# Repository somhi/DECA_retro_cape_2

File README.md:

# DECA Retro Cape 2

### (2 layer - MiSTer module SDRAM version)

DECA Retro Cape 2 is an addon for the [DECA FPGA](https://github.com/DECAfpga/DECA_board) development kit from Arrow/Terasic. The addon is connected to the Beaglebone Black connectors and hence the name of Cape as addons in the Beaglebone world are known.

This cape adds IO interface to the DECA board with all is needed to implement retro computers in this beautiful FPGA. Main IO interfaces are DB15 for VGA, PS2 for keyboard and mouse, DB9 for joystick, MiSTer memory connector, MiSTer user port.

Project has been developed with KiCAD 6.0. 

### Status

STATUS (29/01/23): Tests of v0.90 PCB work as expected, except for JP8 jumper (see [testing notes](testing_v0.90.md)). 

STATUS (26/12/22):  Finalized design v0.90 and production files including BOM and CPL.  See end of readme for changelog improvements from v0.71.

STATUS (07/04/22):  PCBs v0.71 received. Started [testing](testing.md).  Do not use without modifying voltage protections. Keyboard and Joystick (DB9 and USB3) protections must be redesigned in the next release.

STATUS (15/03/22):  prototype desing work finished. v0.71 gerbers sent to JLCPCB for manufacturing.

### Credits

I want to give credits to Tom Verbeure from whom I've taken his [original design  files](https://github.com/tomverbeure/arrow_deca_retro_cape) and adapted to my own design. Not much have been left from his design, but the name "DECA Retro Cape" remains.  

Thanks to rest of Hard Team DECA (C.Palmero & Rhoderik) and Telegram groups for the support received  during the development phase.

### **Schematic**

 [arrow_deca_retro_cape.pdf](arrow_deca_retro_cape.pdf) 

### **Features**

* VGA DAC 444
  *  Jumper to make use of VGA to SCART cables for 15 kHz RGB video

* Terasic 2x20 pin connector (for Mister SDRAM modules) + 3 pin for Dual SDRAM/SRAM 
* PS2 keyboard & mouse connectors
* Double Pmod (1/2) for peripherals (VGA Pmod, Hyperram, ...). 
  * Added four central pins for compatibility with RGB module of MuseLabs

* Pmod 3 (SPI + UART). Can act as Pmod host or peripheral 
* DETO Pmod (6 pin) for general usage (3 multiplexed pins)
* Game controller port (selection jumper to enable one or the other)
  * DB9 connector for joystick (Sega megadrive) (solder JP3 for A.Villena MiSTer DB9 addons)
  * USB3 User Port (for SNAC adapters SNES, Atari, ...)

* UART (Rx/Tx) header
* Power supply headers (5V, 3V3, 3V3 LDO, 2V5 LDO, 1V8 analog)

### **Important Usage notes**

* **Better do not connect/disconnect interfaces while the board is powered**
* **Do not connect two devices simultaneously into DB9 and USB3. Doing so may lead to unpredictabily results and damage the FPGA board**
* Prior to first power on it is required to solder jumpers JP2 (pins 3V3 and V) and JP7 (pin 5V and central pin). Read jumper selection notes below
* To use MiSTer memory modules place jumper JP6 to power supply 3V3 (and better left JP5 without jumper)
* Place jumper JP8 on desired interface (DB9 or USB3) for joystick usage. For USB3 jumper JP9 default is I/O.
* For USB3 SNAC adapters **do not** use the [SNAC level shifter adapter](https://manuferhi.com/p/snac-adapter-for-mister) as voltage protection is already included in the cape.
* For the rest of jumpers read jumper selection notes below. In case of doubt leave the default recommended position.
* There are a few signals with shared functions that cannot be used at the same time. Those signals are indicated in the PCB silkscreen with ( ) or *, **:
  * (1), (2) are shared between DETO PMOD and PMOD2
  * (3) is shared between DETO PMOD and the MUX signal of DB9 when JP3 is soldered
  * "**" only either DB9 or USB3 connector can be used at the same time (select it by jumper JP8)
  * "*" signals MISO, MOSI, CS2, SCK are shared between PMOD3 and the four pins of J2 and J3 located between pmods 2 & 3

### **Jumper Selection**

Defaults are OPEN (jumper not placed or not soldered) and CLOSED (jumper placed or soldered)

* JP1 jumper select Pmod 3 mode as peripheral (no jumper) or host (with jumper) [default is open]

* JP2 solder jumper selects 3V3 power supply from Deca board or from an optional LDO [default 3V3]. An optional 5V to 3V3 LDO can be soldered if the board cannot cope with the connected loads.

* JP3 solder jumper enables compatibility with Antonio Villena's MiSTer DB9 addons if soldered (MUX signal to allow two joysticks). Be careful, THIS OPTION IS UNTESTED [default open]

* JP4 jumper closed enables 5V at VGA pin 9 to make use of VGA to SCART cables for 15 kHz RGB video [default open]

* JP5 jumper closed power supply 2x20 Terasic connector with +5V [default open]

* JP6 jumper closed power supply 2x20 Terasic connector with +3V3 [default closed]

* JP7 solder jumper to select joystick power supply (5V or 2V5) [default 5V]

* JP8 jumper select either DB9 interface or USER IO (USB3). **Only one device can be connected at a time, otherwise might be damaged the FPGA board**

* JP9 jumper select USER IO pin 9 function (signal I/O or 3V3 power) [default I/O]

### 3D model

### Changelog

v0.5  routed finalized

v0.6  MiSTer SDRAM only version. Changed to 2 layer board.

v0.62 all finished except VGA R2R schematic and routing

v0.65 power header changed, minor aesthetic changes

v0.68 added vga schematic and indiv. R 0805 into layout

v0.70 routing finished including vga

v0.71 finished prototype desing. Gerber sent to JLCPCB for manufacturing

v0.72 updated pinout spreadsheet and Readme with testing notes and improvements to be done

v0.75 Improvements from testing phase. 

* Changed footprint DB15 VGA to fit connectors from Aliexpress (was needed to bend pins)

* DETO Pmod connector change to socket type instead of pin type

* Silkscreen improvements: OSHW logo top

* Removed JTAG footprint

* Change limiting resistor of 180 Ohm to 510 Ohm (ps2 and db9)

* Power header reduced to 1 row instead of 2

* Optimized some traces

* Added solder pad JP3 to enable/disable compatibility with Antonio Villena's MiSTer DB9 addons

* JP4 jumper to enable 5V at VGA pin 9 to make use of VGA to SCART cables for 15 kHz RGB video

* Added PCB Hole for seeing Conf_done, Rx, Tx leds

v0.76 Double pmod 1&2 now compatible with pmod RGB module of MuseLabs (added 4 shared pins)

v0.77 Changes:

* Terasic connector: add jumpers on 5V and 3V3 to disconnect power, so I can connect it to other Terasic powered connectors.
* Replaced 3 pin jumper JP2 with solder jumper on 3V3 power selection
* Added solder jumper to select joystick power supply (5V or 2V5 from LDO)

v0.78 Changes:

* PS2 protection usign 3V9 Zener diodes (3V7 to 4V1).

* Added pulldown optional resistors for ps2 mouse

v0.80 Added Joystick shifter level protection with IC [TXS0108E](https://jlcpcb.com/partdetail/TexasInstruments-TXS0108EPWR/C17206) and jumper JP8 to select either DB9 or USB3 IO interface

v0.81 Improved Readme. Added readme notice in silkscreen. Removed v0.78 pulldown optional resistors for ps2 mouse (one of the pins has a physical pull-up resistor in fpga, so wouldn't work).

v0.82 generated BOM before installing jlcpcb-tools plugin

v0.83 Added jlcpcb parts with jlcpcb tools plugin 

v0.84 updated USB3 footprint

v0.85 updated references folder. choose zener 3V9 reference 

v0.86 updated datasheets, added R7 1Ω for increasing ESR on 2V5 LDO output with a ceramic capacitor instead of tantalum, updated BOM and nearly finished jlcpcb parts selection

v0.87 updated readme. Minor changes on schematic and PCB 

v0.90 Finalized design v0.90 and production files including BOM and CPL

### TODO improvements

* Reduce lenght of board in VGA wing side
* PS2:  Jumpers to activate pull-down resistors to enable USB mode
* If space is needed, make a common ps2 connector for keyb and mouse (ps2 splitter should be used). 
* Jumper on joystick DB9 pin 5 to change power supply to pin 7 in order to allow other joysticks like the Amiga one to work. Comment from telegram: "El Jumper lo puedes poner para cambiar la alimentación entre pin 5 y 7. De esa forma te funcionara ok los dos y podrás conectar cosas como el ratón de amiga. De los joysticks clásicos, la mayoría son totalmente pasivos y los quickshot II utilizan la alimentación de 5v para el autofire."
* SDRAM DQ14 and DQ15 position in newer MiSTer modules (xsds) are exchanged respect the older module (xs) I based my design from. This does not affect functionality at all as data in and data out are always in the same order.

### Testing

[Testings on v0.71 PCB](testing_v0.71.md)

[Testings on v0.90 PCB](testing_v0.90.md)

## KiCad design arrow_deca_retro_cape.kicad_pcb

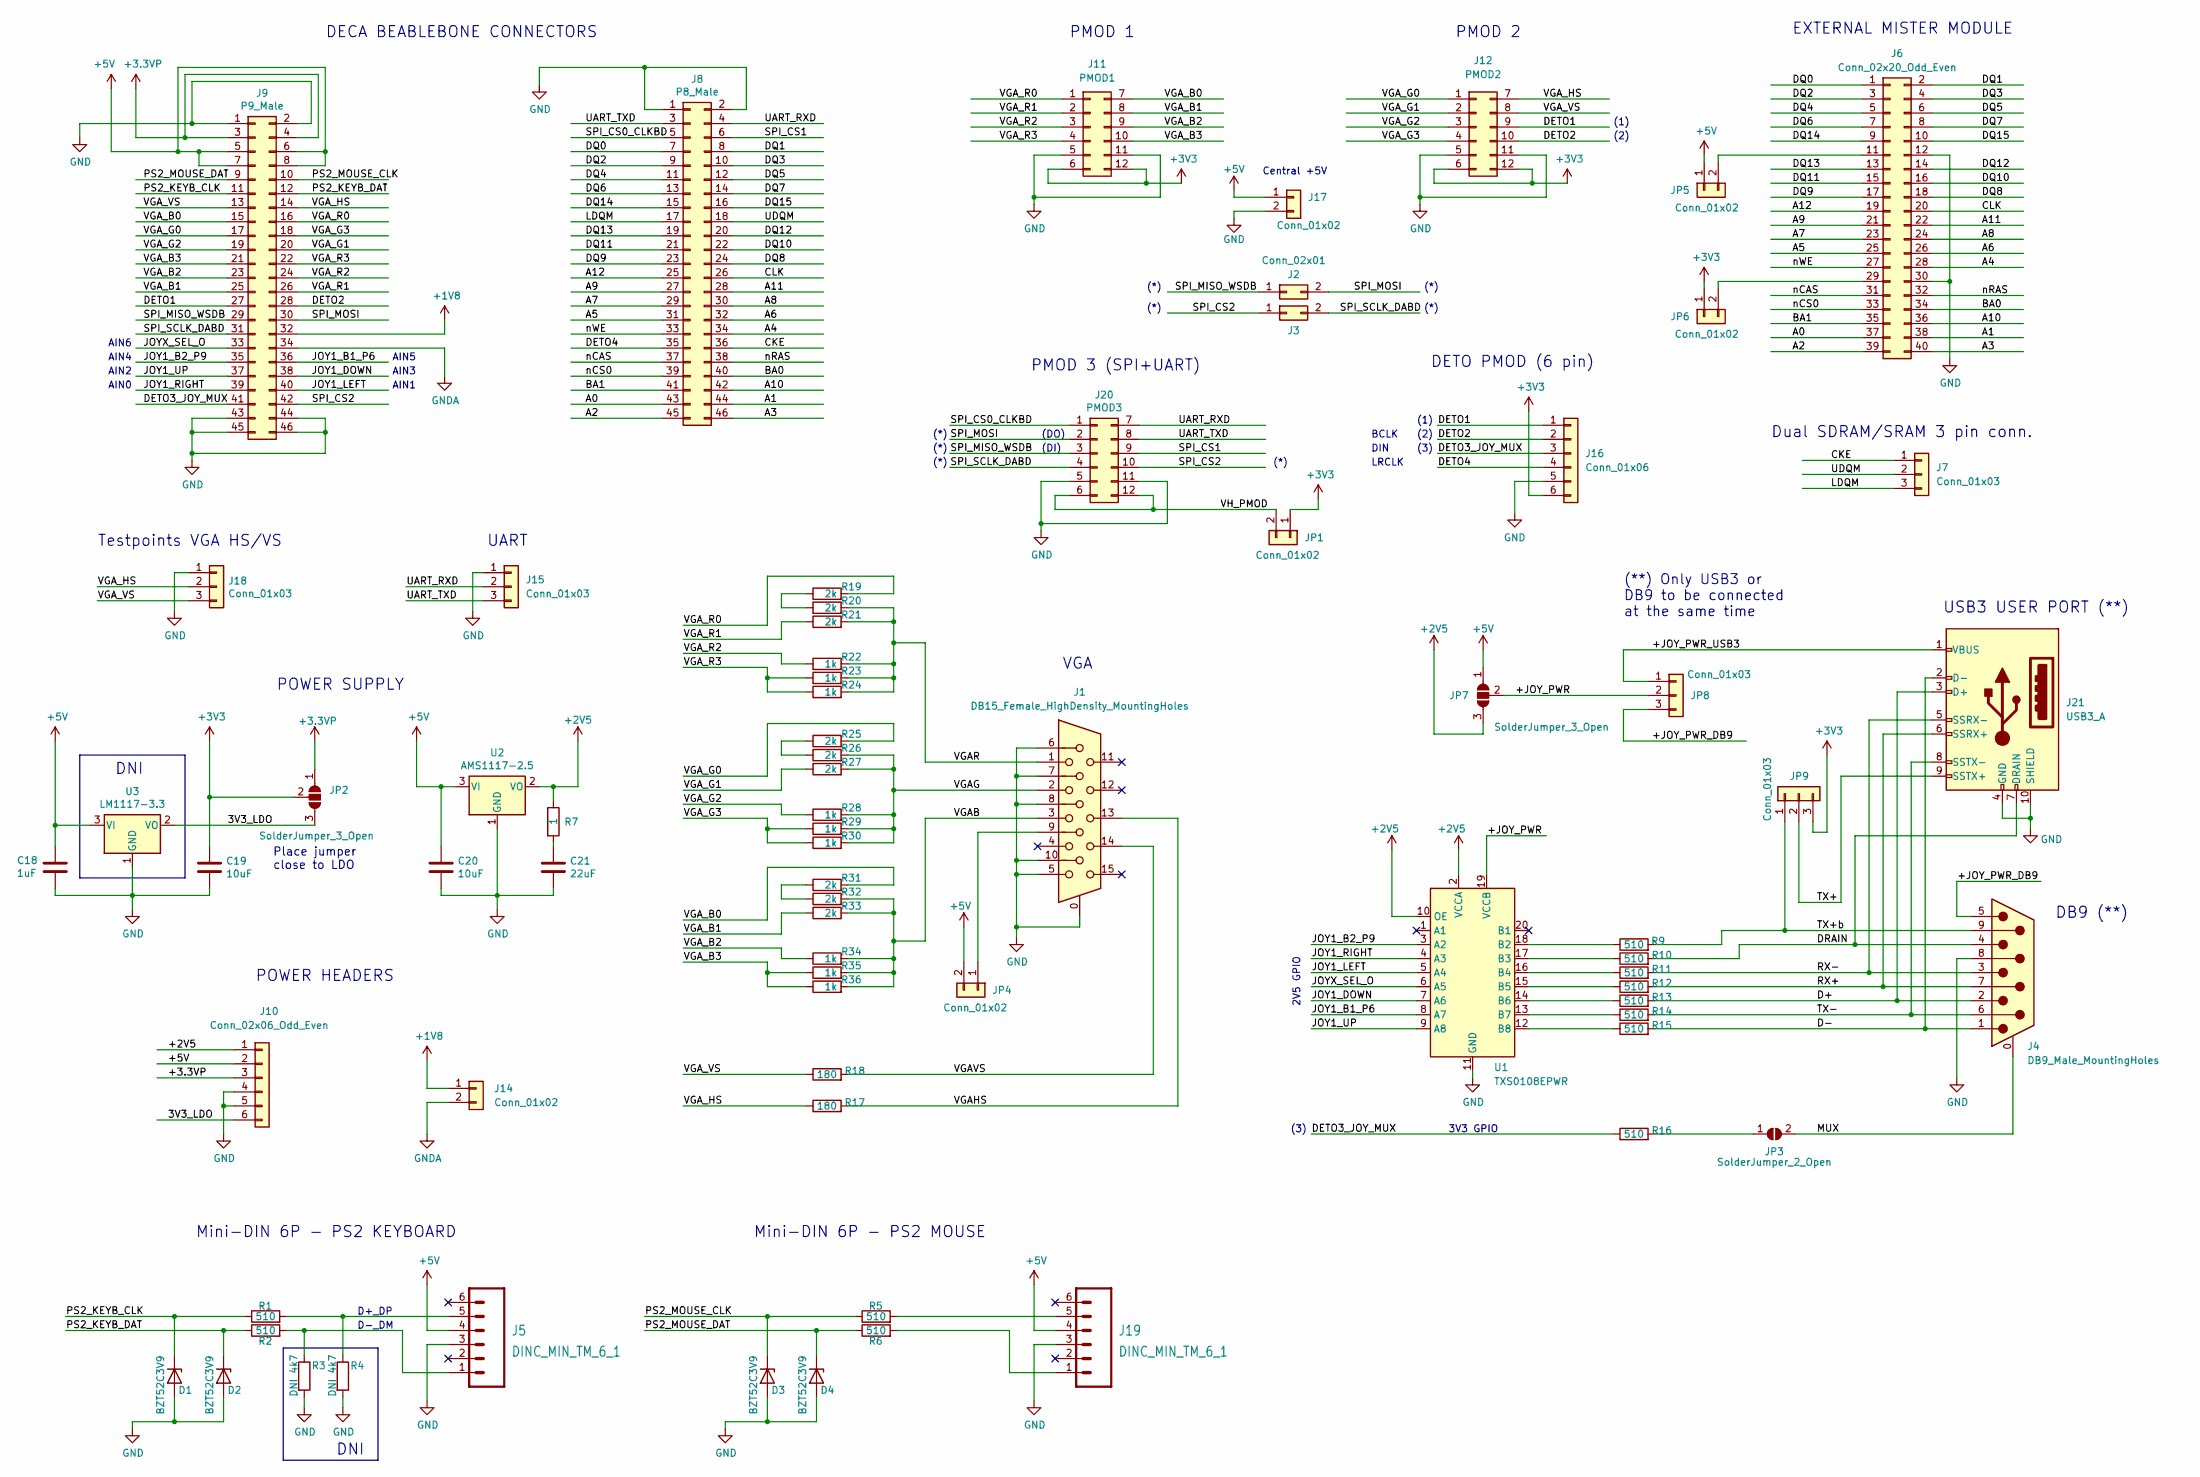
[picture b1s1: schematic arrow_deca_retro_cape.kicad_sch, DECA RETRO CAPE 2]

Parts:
C18: 1uF; C_0805_2012Metric_Pad1.18x1.45mm_HandSolder
C19, C20: 10uF; C_0805_2012Metric_Pad1.18x1.45mm_HandSolder
C21: 22uF; C_0805_2012Metric_Pad1.18x1.45mm_HandSolder
D1, D2, D3, D4: BZT52C3V9; D_SOD-123
J1: DB15_Female_HighDensity_MountingHoles; DSUB-15-HD_Female_Horizontal_P2.29x1.98mm_EdgePinOffset3.03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
J2, J3: Conn_02x01; PinSocket_1x02_P2.54mm_Vertical
J4: DB9_Male_MountingHoles; DSUB-9_Male_Horizontal_P2.77x2.84mm_EdgePinOffset9.90mm_Hou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
J5, J19: DINC_MIN_TM_6_1; DINC_MIN_TM_6_1PRIMARY
J6: Conn_02x20_Odd_Even; PinHeader_2x20_P2.54mm_Vertical
J7: Conn_01x03; PinSocket_1x03_P2.54mm_Vertical
J8: P8_Male; PinHeader_2x23_P2.54mm_Vertical
J9: P9_Male; PinHeader_2x23_P2.54mm_Vertical
J10: Conn_02x06_Odd_Even; PinSocket_1x06_P2.54mm_Vertical
J11: PMOD1; Pmod_2x06_P2.54mm_Vertical_2
J12: PMOD2; Pmod_2x06_P2.54mm_Vertical_2
J14, J17: Conn_01x02; PinSocket_1x02_P2.54mm_Vertical
J15, J18: Conn_01x03; PinHeader_1x03_P2.54mm_Vertical
J16: Conn_01x06; PinSocket_1x06_P2.54mm_Vertical
J20: PMOD3; PMOD_Female_Horizontal_2
J21: USB3_A; USB-3.0-TH_C69073
JP1, JP4, JP5, JP6: Conn_01x02; PinHeader_1x02_P2.54mm_Vertical
JP2, JP7: SolderJumper_3_Open; SolderJumper-3_P2.0mm_Open_TrianglePad1.0x1.5mm
JP3: SolderJumper_2_Open; SolderJumper-2_P1.3mm_Open_RoundedPad1.0x1.5mm
JP8, JP9: Conn_01x03; PinHeader_1x03_P2.54mm_Vertical
R1, R2, R5, R6, R9, R10, R11, R12, R13, R14, R15, R16: 510; R_0805_2012Metric_Pad1.20x1.40mm_HandSolder
R3, R4: DNI 4k7; R_0805_2012Metric_Pad1.20x1.40mm_HandSolder
R7: 1; R_0805_2012Metric_Pad1.20x1.40mm_HandSolder
R17, R18: 180; R_0805_2012Metric_Pad1.20x1.40mm_HandSolder
R19, R20, R21, R25, R26, R27, R31, R32, R33: 2k; R_0805_2012Metric_Pad1.20x1.40mm_HandSolder
R22, R23, R24, R28, R29, R30, R34, R35, R36: 1k; R_0805_2012Metric_Pad1.20x1.40mm_HandSolder
U1: TXS0108EPWR; TSSOP-20_4.4x6.5mm_P0.65mm
U2: AMS1117-2.5; SOT-223-3_TabPin2
U3: LM1117-3.3; SOT-223-3_TabPin2

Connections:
+1V8: J9.32, J14.1
+2V5: J10.1, JP7.3 (B), R7.1, U1.2 (VCCA), U1.10 (OE), U2.2 (VO)
+3.3VP: J9.3, J9.4, J10.3, JP2.1 (A)
+3V3: C19.1, J11.6, J11.12, J12.6, J12.12, J16.6, JP1.1, JP2.2 (C), JP6.1, JP9.3
+5V: C18.1, C20.1, J5.4, J9.5, J9.6, J9.7, J9.8, J10.2, J17.1, J19.4, JP4.2, JP5.1, JP7.1 (A), U2.3 (VI), U3.3 (VI)
/3V3_LDO: J10.6, JP2.3 (B), U3.2 (VO)
/+JOY_PWR: JP7.2 (C), JP8.2, U1.19 (VCCB)
/+JOY_PWR_DB9: J4.5, JP8.3
/+JOY_PWR_USB3: J21.1 (VBUS), JP8.1
/A0: J6.37, J8.43
/A1: J6.38, J8.44
/A2: J6.39, J8.45
/A3: J6.40, J8.46
/A4: J6.28, J8.34
/A5: J6.25, J8.31
/A6: J6.26, J8.32
/A7: J6.23, J8.29
/A8: J6.24, J8.30
/A9: J6.21, J8.27
/A10: J6.36, J8.42
/A11: J6.22, J8.28
/A12: J6.19, J8.25
/BA0: J6.34, J8.40
/BA1: J6.35, J8.41
/CKE: J7.1, J8.36
/CLK: J6.20, J8.26
/D+: J4.2, J21.3 (D+), R13.2
/D-: J4.1, J21.2 (D-), R15.2
/DETO1: J9.27, J12.9, J16.1
/DETO2: J9.28, J12.10, J16.2
/DETO3_JOY_MUX: J9.41, J16.3, R16.1
/DETO4: J8.35, J16.4
/DQ0: J6.1, J8.7
/DQ1: J6.2, J8.8
/DQ2: J6.3, J8.9
/DQ3: J6.4, J8.10
/DQ4: J6.5, J8.11
/DQ5: J6.6, J8.12
/DQ6: J6.7, J8.13
/DQ7: J6.8, J8.14
/DQ8: J6.18, J8.24
/DQ9: J6.17, J8.23
/DQ10: J6.16, J8.22
/DQ11: J6.15, J8.21
/DQ12: J6.14, J8.20
/DQ13: J6.13, J8.19
/DQ14: J6.9, J8.15
/DQ15: J6.10, J8.16
/DRAIN: J4.4, J21.7 (DRAIN), R10.2
/JOY1_B1_P6: J9.36, U1.8 (A7)
/JOY1_B2_P9: J9.35, U1.3 (A2)
/JOY1_DOWN: J9.38, U1.7 (A6)
/JOY1_LEFT: J9.40, U1.5 (A4)
/JOY1_RIGHT: J9.39, U1.4 (A3)
/JOY1_UP: J9.37, U1.9 (A8)
/JOYX_SEL_O: J9.33, U1.6 (A5)
/LDQM: J7.3, J8.17
/MUX: J4.0 (PAD), JP3.2 (B)
/PS2_KEYB_CLK: D1.1 (K), J9.11, R1.1
/PS2_KEYB_DAT: D2.1 (K), J9.12, R2.1
/PS2_MOUSE_CLK: D3.1 (K), J9.10, R5.1
/PS2_MOUSE_DAT: D4.1 (K), J9.9, R6.1
/RX+: J4.7, J21.6 (SSRX+), R12.2
/RX-: J4.3, J21.5 (SSRX-), R11.2
/SPI_CS0_CLKBD: J8.5, J20.1
/SPI_CS1: J8.6, J20.9
/SPI_CS2: J3.1, J9.42, J20.10
/SPI_MISO_WSDB: J2.1, J9.29, J20.3
/SPI_MOSI: J2.2, J9.30, J20.2
/SPI_SCLK_DABD: J3.2, J9.31, J20.4
/TX+: J21.9 (SSTX+), JP9.2
/TX+b: J4.9, JP9.1, R9.2
/TX-: J4.6, J21.8 (SSTX-), R14.2
/UART_RXD: J8.4, J15.2, J20.7
/UART_TXD: J8.3, J15.3, J20.8
/UDQM: J7.2, J8.18
/VGAB: J1.3, R32.2, R33.2, R34.2, R35.2, R36.2
/VGAG: J1.2, R26.2, R27.2, R28.2, R29.2, R30.2
/VGAHS: J1.13, R17.2
/VGAR: J1.1, R20.2, R21.2, R22.2, R23.2, R24.2
/VGAVS: J1.14, R18.2
/VGA_B0: J9.15, J11.7, R31.2
/VGA_B1: J9.25, J11.8, R33.1
/VGA_B2: J9.23, J11.9, R34.1
/VGA_B3: J9.21, J11.10, R35.1, R36.1
/VGA_G0: J9.17, J12.1, R25.2
/VGA_G1: J9.20, J12.2, R27.1
/VGA_G2: J9.19, J12.3, R28.1
/VGA_G3: J9.18, J12.4, R29.1, R30.1
/VGA_HS: J9.14, J12.7, J18.2, R17.1
/VGA_R0: J9.16, J11.1, R19.2
/VGA_R1: J9.26, J11.2, R21.1
/VGA_R2: J9.24, J11.3, R22.1
/VGA_R3: J9.22, J11.4, R23.1, R24.1
/VGA_VS: J9.13, J12.8, J18.3, R18.1
/VH_PMOD: J20.6, J20.12, JP1.2
/nCAS: J6.31, J8.37
/nCS0: J6.33, J8.39
/nRAS: J6.32, J8.38
/nWE: J6.27, J8.33
GND: C18.2, C19.2, C20.2, C21.2, D1.2 (A), D2.2 (A), D3.2 (A), D4.2 (A), J1.0, J1.5, J1.6, J1.7, J1.8, J1.10, J4.8, J5.3, J6.12, J6.30, J8.1, J8.2, J9.1, J9.2, J9.43, J9.44, J9.45, J9.46, J10.4, J10.5, J11.5, J11.11, J12.5, J12.11, J15.1, J16.5, J17.2, J18.1, J19.3, J20.5, J20.11, J21.4 (GND), J21.10 (SHIELD), R3.2, R4.2, U1.11 (GND), U2.1 (GND), U3.1 (GND)
GNDA: J9.34, J14.2
unnamed: C21.1, R7.2
unnamed: J1.9, JP4.1
unnamed: J5.1, R2.2, R3.1
unnamed: J5.5, R1.2, R4.1
unnamed: J6.11, JP5.2
unnamed: J6.29, JP6.2
unnamed: J19.1, R6.2
unnamed: J19.5, R5.2
unnamed: JP3.1 (A), R16.2
unnamed: R9.1, U1.18 (B2)
unnamed: R10.1, U1.17 (B3)
unnamed: R11.1, U1.16 (B4)
unnamed: R12.1, U1.15 (B5)
unnamed: R13.1, U1.14 (B6)
unnamed: R14.1, U1.13 (B7)
unnamed: R15.1, U1.12 (B8)
unnamed: R19.1, R20.1
unnamed: R25.1, R26.1
unnamed: R31.1, R32.1

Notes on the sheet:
(*)
D-_DM
POWER HEADERS
Testpoints VGA HS/VS
Dual SDRAM/SRAM 3 pin conn.
AIN2
BCLK
AIN6
Central +5V
PMOD 2
PMOD 1
DB9 (**)
DIN
(**) Only USB3 or DB9 to be connected at the same time
POWER SUPPLY
DNI
2V5 GPIO
LRCLK
(2)
AIN5
DECA BEABLEBONE CONNECTORS
(DI)
AIN0
3V3 GPIO
(3)
AIN4
Place jumper close to LDO
USB3 USER PORT (**)
AIN3
Mini-DIN 6P - PS2 MOUSE
PMOD 3 (SPI+UART)
UART
D+_DP
Mini-DIN 6P - PS2 KEYBOARD
(1)
DETO PMOD (6 pin)
(DO)
EXTERNAL MISTER MODULE
AIN1
VGA

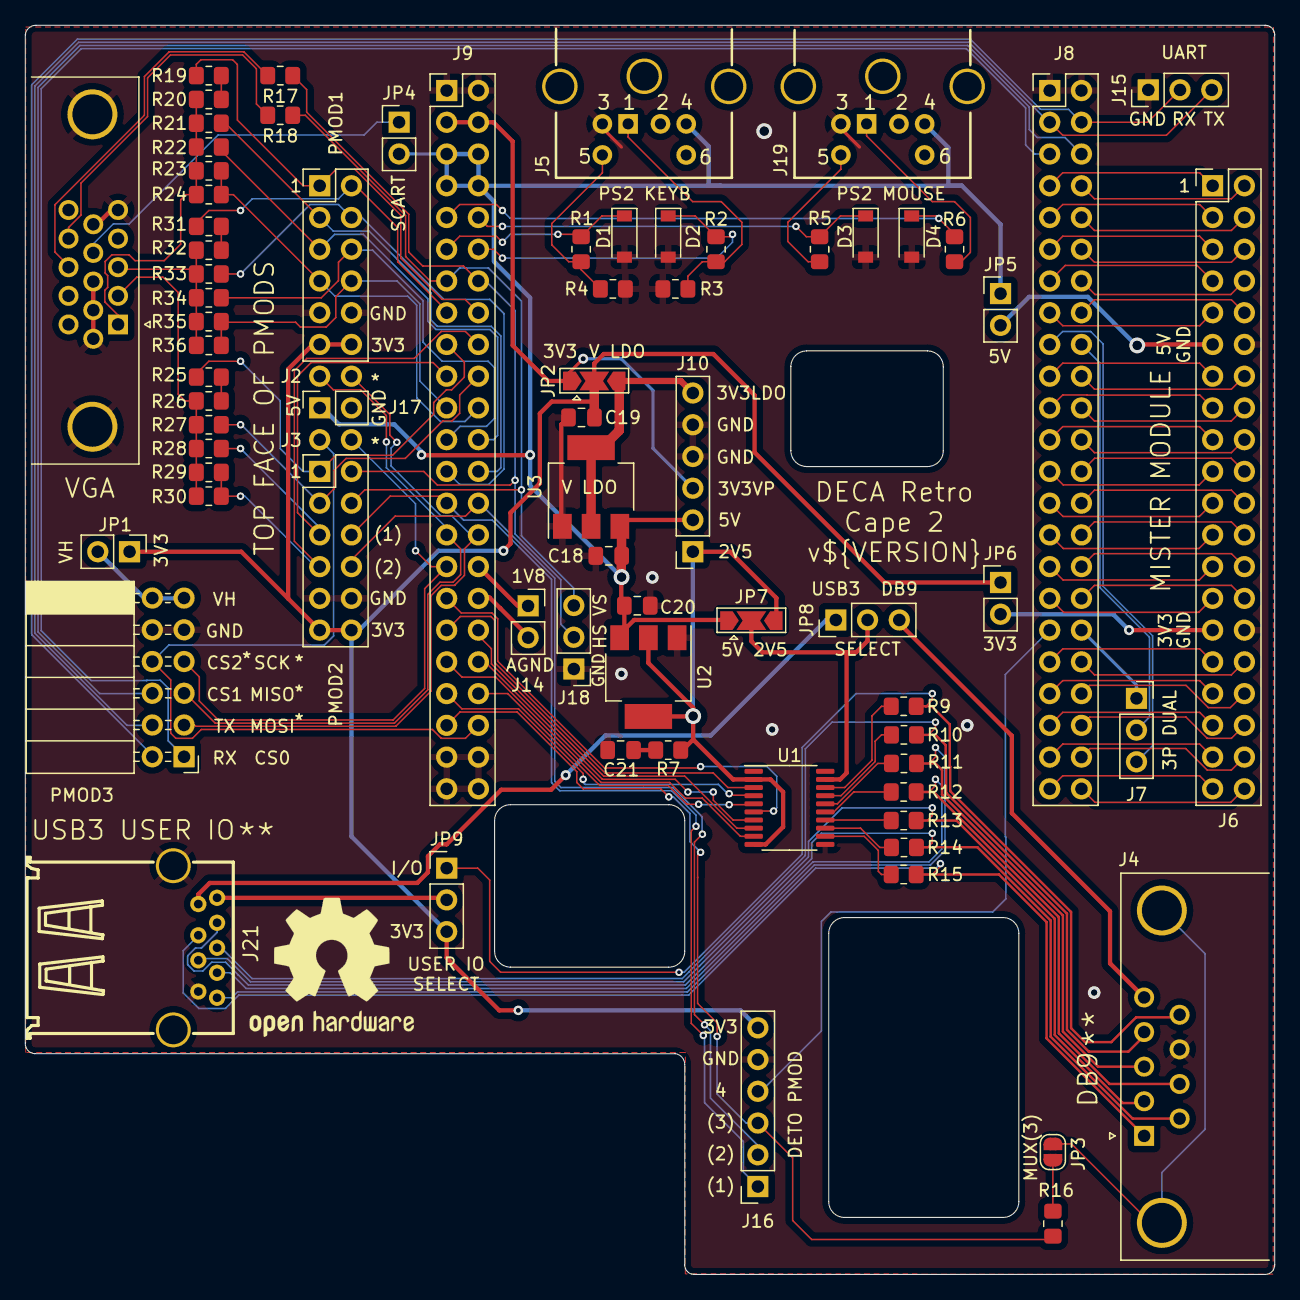
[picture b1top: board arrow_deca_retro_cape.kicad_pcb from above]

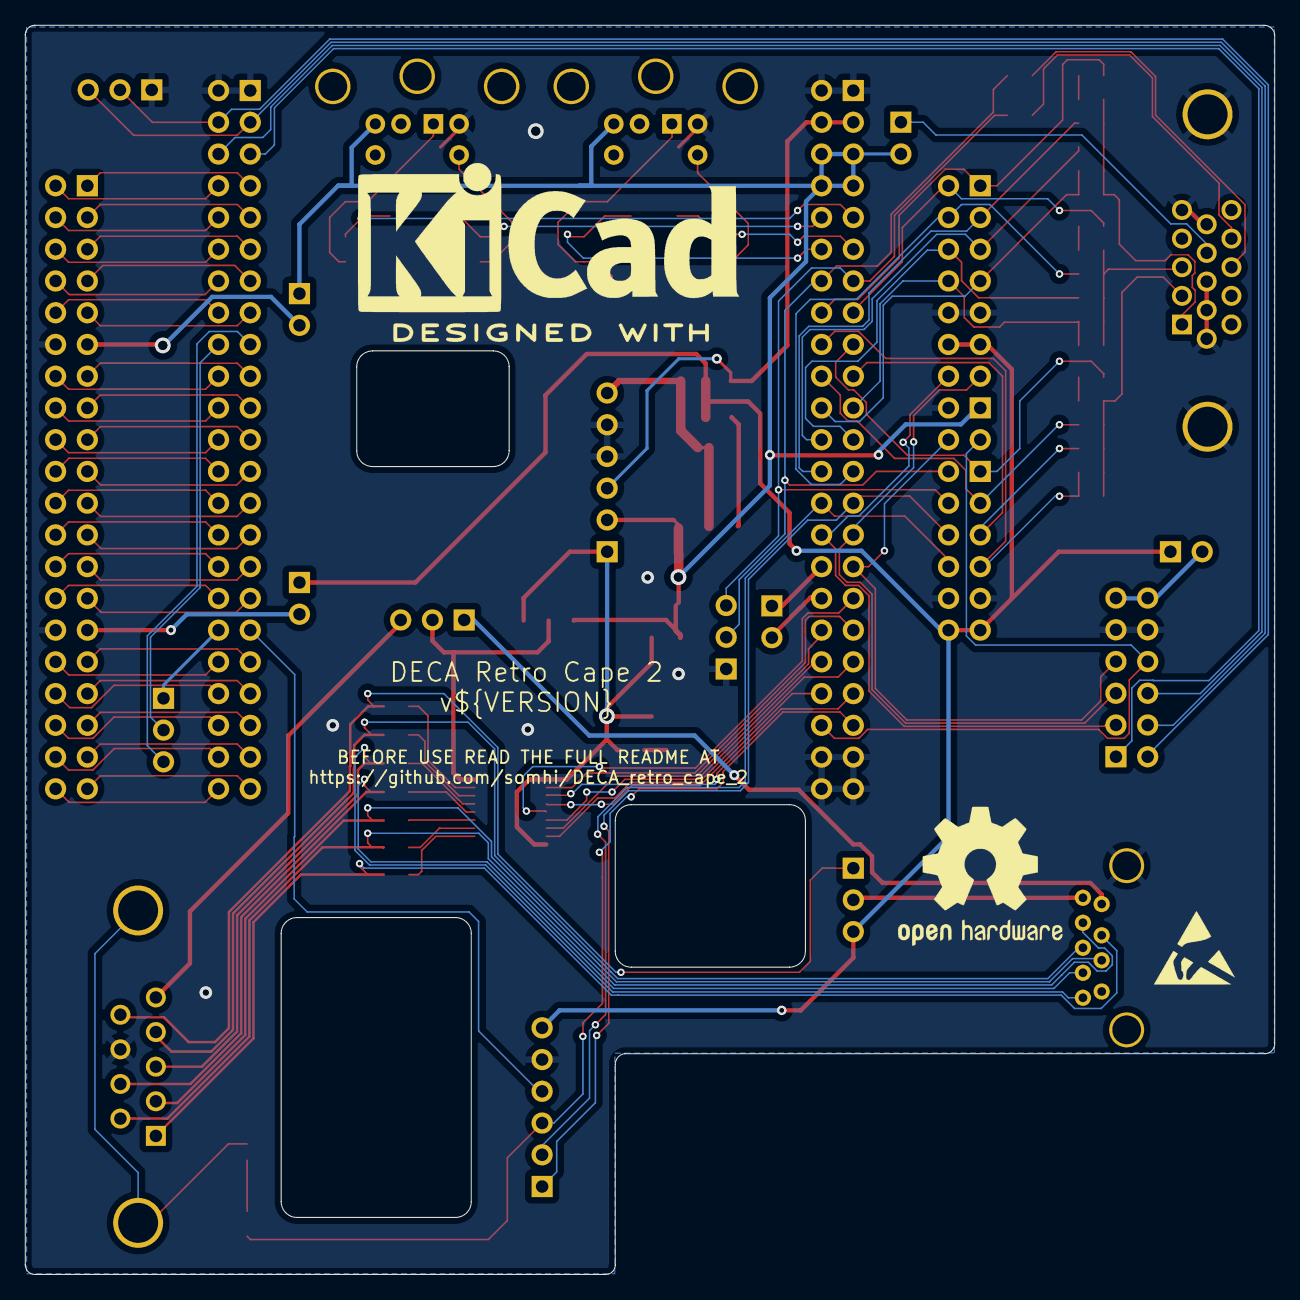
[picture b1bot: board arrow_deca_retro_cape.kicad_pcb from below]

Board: 2 copper layers, 100.0 x 100.0 mm, 79 parts (3 on the bottom side), 121 nets.

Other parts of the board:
LO1: KiCad-Logo2_12mm_SilkScreen
LO2, LO3: OSHW-Logo2_14.6x12mm_SilkScreen
LO4: ESD-Logo_6.6x6mm_SilkScreen

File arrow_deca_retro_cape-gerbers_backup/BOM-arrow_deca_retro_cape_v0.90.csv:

Comment,Designator,Footprint,LCSC
BZT52C3V9,"D1,D2,D3,D4",D_SOD-123,C107594
AMS1117-2.5,U2,SOT-223-3_TabPin2,C12087
10uF,"C19,C20",C_0805_2012Metric_Pad1.18x1.45mm_HandSolder,C15850
TXS0108EPWR,U1,TSSOP-20_4.4x6.5mm_P0.65mm,C17206
1k,"R22,R23,R24,R28,R29,R30,R34,R35,R36",R_0805_2012Metric_Pad1.20x1.40mm_HandSolder,C17513
2k,"R19,R20,R21,R25,R26,R27,R31,R32,R33",R_0805_2012Metric_Pad1.20x1.40mm_HandSolder,C17604
510,"R1,R10,R11,R12,R13,R14,R15,R16,R2,R5,R6,R9",R_0805_2012Metric_Pad1.20x1.40mm_HandSolder,C17734
180,"R17,R18",R_0805_2012Metric_Pad1.20x1.40mm_HandSolder,C25270
1,R7,R_0805_2012Metric_Pad1.20x1.40mm_HandSolder,C25271
1uF,C18,C_0805_2012Metric_Pad1.18x1.45mm_HandSolder,C28323
22uF,C21,C_0805_2012Metric_Pad1.18x1.45mm_HandSolder,C45783

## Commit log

2022-03-11 v0.61 2-layer. Edge removed
2022-03-13 v0.62 only vga routing missing
2022-03-13 v0.62 added 3d pictures
2022-03-13 v0.62 readme
2022-03-13 v0.62 final without vga
2022-03-13 v0.65 power header changed
2022-03-13 v0.68 vga schematic
2022-03-13 v0.7 routing finished including vga
2022-03-13 updated readme and routing improvement
2022-03-15 v0.71 gerbers sent for manufacturing
2022-04-09 updated status. received pcb. started testing
2022-04-12 updated materials list
2022-05-03 v0.72 updated readme and pinout spreadsheet
2022-11-24 v0.75 see changelog
2022-11-24 v0.76 double pmod added 4 central pins
2022-11-26 v0.77 see changelog
2022-11-27 v0.78 ps2 protections with zeners
2022-12-08 v0.80 WIP adding level shifter for db9/usb3
2022-12-08 v0.8 routing ended for level shifter
2022-12-09 v0.81 minor updates. Improved readme
2022-12-16 v0.82 generated BOM before install. jlcpcb-tools plugin
2022-12-22 v0.83 Added jlcpcb parts with jlcpcb tools plugin
2022-12-22 v0.84 updated USB3 footprint
2022-12-24 v0.85 reorganized references. Added Zener 3V9 reference
2022-12-24 v0.86 updated datasheets, added R7
2022-12-25 v0.87 updated readme and minor changes sch&pcb
2022-12-26 v0.90 finalized gerger, bom and cpl files ready for jlcpcb production
2023-01-23 Updated JLCPCB BOM, deleted gerber files not used
2023-01-29 added testing notes v0.9 and updated readme
2023-01-31 updated BOM of v0.90
2023-02-05 update comments on DECA pinout
2023-03-03 minor schematic notes update
2023-03-03 updated readme regarding sdram DQ14 & DQ15 pins exchanged in newer MiSTer modules
2023-04-01 pinout update sigma_l, sigma_r
2023-04-02 minor readme update
2023-05-30 updated readme and minor pinout

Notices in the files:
arrow_deca_retro_cape.kicad_pcb:
License: CC-BY-SA v4.0
